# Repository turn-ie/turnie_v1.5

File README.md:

# turnie v1.5

Waveshare **ESP32-S3-Matrix**（8x8 LED）に自作のシールド基板を重ねた turnie。
すれ違った turnie どうしで、BLE5 拡張アドバタイズを使ってピクセルアートや文字を交換する。
基板、筐体（HP MJF PA12 ＋ アクリルの天板）、ファームウェアをまとめたリポジトリ。

## ディレクトリ構成

| ディレクトリ | 内容 |
|---|---|
| `hardware/` | KiCad プロジェクト（シールド基板 r2）、BOM、ガーバー（`production/`）、回路図 PDF（`out_20261115/`） |
| `enclosure/case_r2_20261120/` | 筐体 r2（STEP と、生成・干渉確認用の CadQuery スクリプト） |
| `enclosure/fdm_20261119/` | FDM 試作用の筐体（STEP、STL、スクリプト） |
| `firmware/` | ファームウェア（PlatformIO、ESP32-S3）。通信仕様は `firmware/COMMUNICATION_SPEC.md` |

## ハードウェア

| 部品 | 内容 |
|---|---|
| MCU / LED | Waveshare ESP32-S3-Matrix（8x8 WS2812B、IMU QMI8658） |
| 充電 | MCP73831（USB-C はモジュールの受け口を使う） |
| 電源 | SW2 スライドスイッチ ＋ SW1 で入る電源ラッチ（Q1 P-FET、IO2 で保持） |
| ボタン SW1 | 一般的な 6x6 mm タクトスイッチ（高さ 5 mm）＋ 3D プリントのキャップ |
| 電池 | LiPo 36 x 24.5 x 5.6 mm |
| 筐体 | 42.99 x 30.93 x 17.60 mm、HP MJF PA12、天板はアクリル 2.0 mm |

## 関連リポジトリ

- [turnie_device_v1.5](https://github.com/turn-ie/turnie_device_v1.5)：v1.5 のファームウェア（このリポジトリの `firmware/` は r2 基板向けの版）
- [turnie_app](https://github.com/turn-ie/turnie_app)：iOS アプリ
- [turnie_garber](https://github.com/turn-ie/turnie_garber)：初期のシールド基板のガーバー

## 備考

- 画像は KiCad の 3D ビュー（シールド基板 r2 ＋ ESP32-S3-Matrix）。

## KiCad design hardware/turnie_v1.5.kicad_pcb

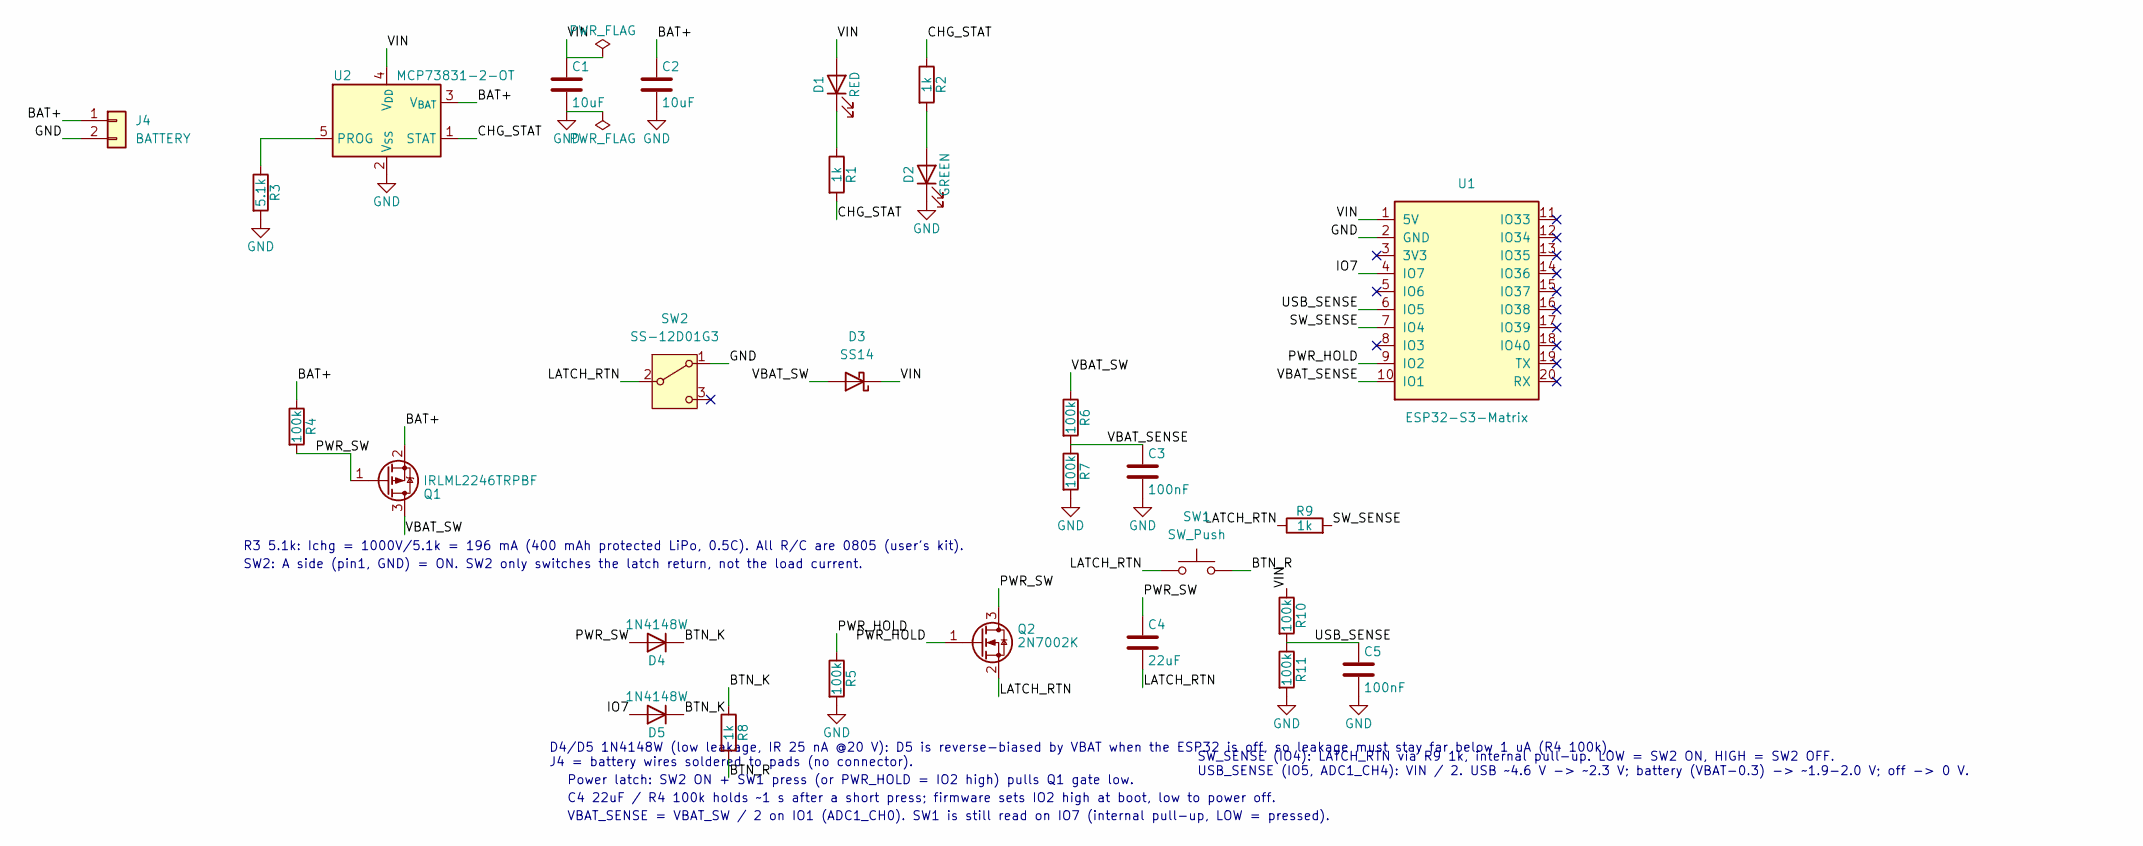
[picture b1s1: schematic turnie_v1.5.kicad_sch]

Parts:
C1, C2: 10uF; C_0805_2012Metric_Pad1.18x1.45mm_HandSolder; MPN 0805 10uF ≥10V X5R/X7R
C3, C5: 100nF; C_0805_2012Metric_Pad1.18x1.45mm_HandSolder; MPN 0805 100nF
C4: 22uF; C_0805_2012Metric_Pad1.18x1.45mm_HandSolder; MPN 0805 22uF ≥10V X5R/X7R
D1: RED; LED_0805_2012Metric_Pad1.15x1.40mm_HandSolder; MPN OSR50805C1C
D2: GREEN; LED_0805_2012Metric_Pad1.15x1.40mm_HandSolder; MPN OSG50805C1C
D3: SS14; D_SMA; MPN SS14
D4, D5: 1N4148W; D_SOD-123; MPN 1N4148W (PANJIT) SOD-123
J4: BATTERY; SolderPads_Battery_1x02_P2.54mm_Drill1.0mm; MPN solder pads, 1=BAT+ 2=GND
Q1: IRLML2246TRPBF; SOT-23; MPN IRLML2246TRPBF
Q2: 2N7002K; SOT-23; MPN 2N7002K
R1, R2, R8, R9: 1k; R_0805_2012Metric_Pad1.20x1.40mm_HandSolder; MPN 0805 1k
R3: 5.1k; R_0805_2012Metric_Pad1.20x1.40mm_HandSolder; MPN 0805 5.1k (1% 推奨)
R4, R5, R6, R7, R10, R11: 100k; R_0805_2012Metric_Pad1.20x1.40mm_HandSolder; MPN 0805 100k
SW1: SW_Push; SW_PUSH_6mm_H5mm; MPN generic 6x6x5mm THT tact
SW2: SS-12D01G3; SW_Slide_SPDT_JinBeiLi_SS-12D01G3_Akizuki_115704; MPN SS-12D01G3
U1: ESP32-S3-Matrix; Waveshare_ESP32-S3-Matrix; MPN Waveshare ESP32-S3-Matrix
U2: MCP73831-2-OT; SOT-23-5_HandSoldering; MPN MCP73831T-2ATI/OT

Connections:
/BAT+: C2.1, J4.1, Q1.2 (S), R4.1, U2.3 (V_{BAT})
/BTN_K: D4.1 (K), D5.1 (K), R8.1
/BTN_R: R8.2, SW1.2
/CHG_STAT: R1.2, R2.1, U2.1 (STAT)
/IO7: D5.2 (A), U1.4 (IO7)
/LATCH_RTN: C4.2, Q2.2 (S), R9.1, SW1.1, SW2.2 (B)
/PWR_HOLD: Q2.1 (G), R5.1, U1.9 (IO2)
/PWR_SW: C4.1, D4.2 (A), Q1.1 (G), Q2.3 (D), R4.2
/SW_SENSE: R9.2, U1.7 (IO4)
/USB_SENSE: C5.1, R10.2, R11.1, U1.6 (IO5)
/VBAT_SENSE: C3.1, R6.2, R7.1, U1.10 (IO1)
/VBAT_SW: D3.2 (A), Q1.3 (D), R6.1
/VIN: C1.1, D1.2 (A), D3.1 (K), R10.1, U1.1 (5V), U2.4 (V_{DD})
GND: C1.2, C2.2, C3.2, C5.2, D2.1 (K), J4.2, R3.2, R5.2, R7.2, R11.2, SW2.1 (A), U1.2 (GND), U2.2 (V_{SS})
unnamed: D1.1 (K), R1.1
unnamed: D2.2 (A), R2.2
unnamed: R3.1, U2.5 (PROG)

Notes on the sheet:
SW_SENSE (IO4): LATCH_RTN via R9 1k, internal pull-up. LOW = SW2 ON, HIGH = SW2 OFF. USB_SENSE (IO5, ADC1_CH4): VIN / 2. USB ~4.6 V -> ~2.3 V; battery (VBAT-0.3) -> ~1.9-2.0 V; off -> 0 V.
D4/D5 1N4148W (low leakage, IR 25 nA @20 V): D5 is reverse-biased by VBAT when the ESP32 is off, so leakage must stay far below 1 uA (R4 100k). J4 = battery wires soldered to pads (no connector).
SW2: A side (pin1, GND) = ON. SW2 only switches the latch return, not the load current.
R3 5.1k: Ichg = 1000V/5.1k = 196 mA (400 mAh protected LiPo, 0.5C). All R/C are 0805 (user's kit).
C4 22uF / R4 100k holds ~1 s after a short press; firmware sets IO2 high at boot, low to power off.
Power latch: SW2 ON + SW1 press (or PWR_HOLD = IO2 high) pulls Q1 gate low.
VBAT_SENSE = VBAT_SW / 2 on IO1 (ADC1_CH0). SW1 is still read on IO7 (internal pull-up, LOW = pressed).

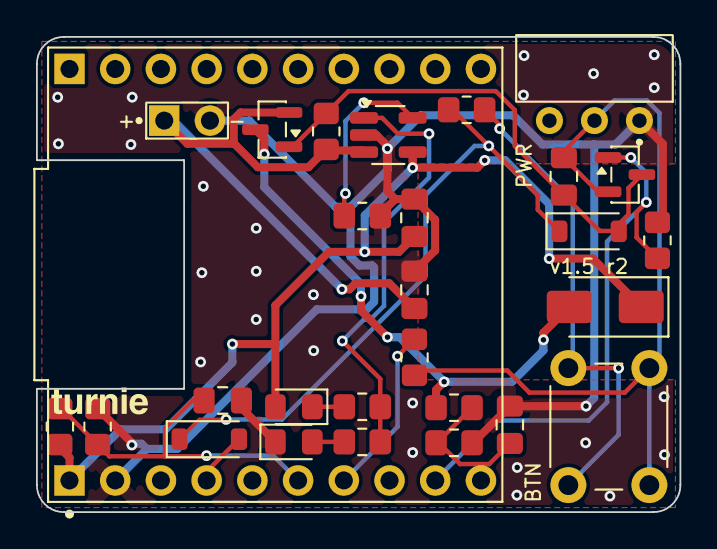
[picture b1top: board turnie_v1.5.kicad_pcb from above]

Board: 2 copper layers, 35.8 x 26.4 mm, 28 parts (0 on the bottom side), 17 nets.

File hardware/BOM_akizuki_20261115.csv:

Ref,値,秋月コード,品名（秋月の表記）,メーカー型番,パッケージ/フットプリント,1枚あたり個数,販売単位と価格(税込),備考
U2,MCP73831-2,113288,超小型単セル用リチウムイオン・リチウムポリマー充電コントローラー MCP73831-2ATI/OT,MCP73831T-2ATI/OT,SOT-23-5 (HandSoldering),1,¥120/1個,
Q1,IRLML2246TRPBF,106048,PchMOSFET IRLML2246TRPBF,IRLML2246TRPBF,SOT-23,1,¥250/10個,AO3401A は秋月に無いため置換。ピン 1=G 2=S 3=D、Vgs(th) -0.4〜-1.1V
Q2,2N7002K,104256,NchMOSFET 60V300mA 2N7002K,2N7002K (PANJIT),SOT-23,1,¥200/40個,
D1,赤LED,106419,赤色チップLED 2012 625nm 150mcd,OSR50805C1C,0805 (2012),1,¥150/10個,充電中に点灯
D2,緑LED,106423,緑色チップLED 2012 525nm 400mcd,OSG50805C1C,0805 (2012),1,¥200/10個,充電完了で点灯
D3,SS14,113240,表面実装用ショットキーバリアダイオード 40V1A SS14,SS14 (PANJIT),SMA,1,¥150/20個,
"D4,D5",1N4148W,116985,高速スイッチング・ダイオード 1N4148W,1N4148W (PANJIT),SOD-123,2,¥160/40個,逆電流 最大 25nA @20V (25℃)、150℃で最大 30µA @25V。BAT54CT の置き換え
"R1,R2,R8,R9",1kΩ,手持ちキット,0805 チップ抵抗,—,0805 (2012),4,—,秋月では購入しない
R3,5.1kΩ,手持ちキット,0805 チップ抵抗（1% 推奨）,—,0805 (2012),1,—,充電電流 約196mA
"R4,R5,R6,R7,R10,R11",100kΩ,手持ちキット,0805 チップ抵抗,—,0805 (2012),6,—,
"C1,C2",10µF,手持ちキット,0805 積層セラミック ≥10V X5R/X7R,—,0805 (2012),2,—,モジュール下に入るので厚さ 1.25mm 以下
"C3,C5",100nF,手持ちキット,0805 積層セラミック,—,0805 (2012),2,—,
C4,22µF,手持ちキット,0805 積層セラミック ≥10V X5R/X7R,—,0805 (2012),1,—,電源ラッチの保持用
SW1,タクトスイッチ,,一般的な 6×6 mm タクトスイッチ（背の低い型、高さ 5 mm）,generic 6x6x5mm THT tact,THT 6×6×5mm 4ピン（SW_PUSH_6mm_H5mm）,1,手持ち,2026-11-20 に 9.5 mm（TVDP01-095BB1、117166）から変更。足の配置 6.5×4.5mm は同じ。上に 3DP のキャップ（Fusion「turnie_ボタン修正版」のスイッチカバーv2_3.7）
SW2,スライドスイッチ,115704,スライドスイッチ 1回路2接点 基板用 横向き SS-12D01G3,SS-12D01G3,THT 3ピン 2.5mm,1,¥20/1個,定格 30V 0.3A（ラッチの戻り線だけを切るので負荷電流は流れない）
J4,電池の線,不要,（コネクタなし。電池の線を穴に直接はんだ付け）,—,THT パッド 2 個 2.54mm,—,—,1=BAT+（角パッド）、2=GND。モジュールを付ける前にはんだ付けする
(U1取付),2.54mmピンヘッダー,100167,ピンヘッダー 1×40 (40P),PH-1x40SG,10ピン×2に切って使用,1,¥35/1個,商品ページは未確認（一覧のみで確認）
U1,ESP32-S3-Matrix,秋月に無し,Waveshare ESP32-S3-Matrix,—,モジュール,1,—,スイッチサイエンス等で購入
BT,LiPo 400mAh 保護回路付き,秋月に無し,(v4 と同じ電池),—,—,1,—,秋月では保護回路付き LiPo を見つけられず

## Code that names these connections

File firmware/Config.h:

#pragma once
#include <Arduino.h>

// ============================================================
// Hardware Pins
// ============================================================
constexpr int PIN_MATRIX = 14;   // NeoMatrix データ
constexpr int PIN_BTN_BOOT = 0;  // BOOT ボタン（GPIO0）。v1.5r2 ではモジュールの裏で基板側を向くので、組み立て後は押せない

// v1.5r2 シールド基板（2026-11-15 作り直し、turnie_v1.5/作業記録_20261115_刷新.md 8 章・12.4 節）
constexpr int PIN_BTN_USER   = 7;  // SW1（INPUT_PULLUP、押すと約 0.55 V = LOW）。SW2 が OFF のときは読めない
constexpr int PIN_PWR_HOLD   = 2;  // 電源の保持（H で保持、L で切る）
constexpr int PIN_SW_SENSE   = 4;  // SW2 の状態（INPUT_PULLUP、L = ON、H = OFF）
constexpr int PIN_USB_SENSE  = 5;  // VIN / 2（ADC1_CH4）
constexpr int PIN_VBAT_SENSE = 1;  // 電池電圧（VBAT_SW）/ 2（ADC1_CH0）

// ============================================================
// Power (v1.5r2)
// ============================================================
constexpr float USB_DETECT_MARGIN_V = 0.15f;  // VIN > 電池電圧 + この値 なら USB あり
constexpr float LOW_BATT_OFF_V = 3.50f;       // 電池だけで動いているとき、これを下回ったら切る（3.5 V 前後でモジュールの LDO が持たなくなる）
constexpr int   LOW_BATT_CONFIRM_COUNT = 5;   // 1 秒ごとに読み、この回数続けて下回ったら確定
constexpr unsigned long POWER_OFF_HOLD_MS     = 3000;   // 電池のとき：ボタンをこの時間押し続けると電源を切る
constexpr unsigned long OTA_HOLD_MS           = 5000;   // USB のとき：この時間押してから離すと OTA モード（BOOT 短押しの代わり）
constexpr unsigned long FACTORY_RESET_HOLD_MS = 10000;  // USB のとき：この時間押し続けると初期化（BOOT 長押しの代わり）
// 操作も受信もない状態がこの時間続いたら、電池のときは自分で電源を切る。0 = 使わない。
// すれ違いの受信は電源が入っている間しかできないので、既定では使わない。
constexpr unsigned long AUTO_OFF_MS = 0;

// ============================================================
// Display (8x8 LED Matrix)
// ============================================================
constexpr int MATRIX_WIDTH = 8;
constexpr int MATRIX_HEIGHT = 8;
constexpr int MATRIX_PIXEL_COUNT = MATRIX_WIDTH * MATRIX_HEIGHT;
constexpr int MATRIX_RGB_BYTES = MATRIX_PIXEL_COUNT * 3;

// 明るさは全モード共通で MOTION_BRIGHTNESS（スマホ設定値）を使う。
constexpr uint16_t TEXT_SCROLL_DELAY_MS = 70;

// ============================================================
// Timing
// ============================================================
constexpr unsigned long LOOP_TICK_MS = 16;          // ~60 fps
constexpr unsigned long RX_DISPLAY_HOLD_MS = 4500;  // 受信表示の保持時間
constexpr unsigned long RX_IGNORE_MS = 5000;        // 一度受信したら、この時間は内容に関わらず後続の受信を全て無視する
constexpr unsigned long RX_SAME_REJECT_MS = 180000; // 直前に受け付けたのと同じ内容がこの時間（5分）以内に届いた場合、完全にリジェクトする（表示も保存も返信もしない）。時間を超えれば同じ内容でも改めて受け付ける。

// 受信履歴の閲覧モード（USER ボタン操作）
constexpr unsigned long BROWSE_LONG_PRESS_MS = 800;    // 長押し判定（閲覧モード開始/終了）
constexpr unsigned long BUTTON_DEBOUNCE_MS = 50;       // 短押しのチャタリング除去
constexpr unsigned long BROWSE_TIMEOUT_MS = 30000;     // 無操作でこの時間経過したら通常へ戻る
constexpr unsigned long BOOT_RESET_LONG_PRESS_MS = 1500; // BOOT長押しでJSONデータをリセット

// ============================================================
// Storage (内部フラッシュ - LittleFS)
// ============================================================
constexpr const char *SD_OWN_JSON = "/data.json";

// ============================================================
// BLE Identity
// ============================================================
constexpr const char *BLE_DEVICE_NAME = "turnie"; // デバイスごとに変更
constexpr uint16_t BLE_COMPANY_ID = 0xFFFF;       // turnie 間の識別子

// ============================================================
// BLE5 Extended Advertising
// ============================================================
constexpr uint8_t BLE_EXT_ADV_HANDLE =
    0; // デバイス間ブロードキャスト（non-connectable）
constexpr uint8_t BLE_GATT_ADV_HANDLE =
    1; // スマホ向け GATT 広告（connectable）
constexpr uint32_t BLE_EXT_ADV_INTERVAL = 0x00C0; // 120 ms (n * 0.625 ms)
constexpr int8_t BLE_EXT_ADV_TX_POWER = 8;        // dBm

// BLE5 Extended Scan
constexpr uint16_t BLE_EXT_SCAN_INTERVAL = 0x0050; // 50 ms
constexpr uint16_t BLE_EXT_SCAN_WINDOW = 0x0030;   // 30 ms

// ============================================================
// BLE GATT (smartphone interface)
// ============================================================
constexpr uint16_t GATT_APP_ID = 0;
constexpr const char *GATT_SVC_UUID = "12345678-1234-1234-1234-1234567890ab";
constexpr const char *GATT_RX_UUID = "abcd1234-5678-90ab-cdef-1234567890ab";
constexpr const char *GATT_TX_UUID = "abcd1234-5678-90ab-cdef-1234567890ac";

// ============================================================
// Inbox (received messages, RAM ring buffer)
// ============================================================
constexpr size_t INBOX_CAPACITY = 30;

// ============================================================
// BLE Settings
// ============================================================
// RSSI の閾値（これより弱い信号は無視する）
// 密着状態で -30 ~ -40, 1m離れて -60 程度
// -128 = 実質すべての受信を許可（int8_t の最小値）
constexpr int8_t BLE_RSSI_MIN = -128;

// ============================================================
// Animation Hue & Settings (per-device config)
// ============================================================
// 色相 H は 0–360（度）。スマホ(setting.json)から送られてくる値もこの範囲。
//   turnie1=127(赤ピンク) / turnie2=298(青) / turnie3=6(緑) / turnie4=104(黄)
constexpr uint8_t DEFAULT_BRIGHTNESS_PERCENT = 25;
constexpr uint8_t DEFAULT_MOTION_BRIGHTNESS = (DEFAULT_BRIGHTNESS_PERCENT * 255) / 100;

extern uint16_t MOTION_HUE;
extern uint8_t MOTION_BRIGHTNESS;
extern uint8_t MOTION_ANIM;

constexpr int DEVICE_NAME_MAX = 32;
extern char DEVICE_NAME[DEVICE_NAME_MAX];

// 出身地（スマホ setting.json の hometown）。任意の文字列。
constexpr int HOMETOWN_MAX = 64;
extern char HOMETOWN[HOMETOWN_MAX];

constexpr const char *SD_SETTING_JSON = "/setting.json";
constexpr const char *SD_INBOX_JSON = "/inbox.json";

// OTA / WiFi の認証情報は Secrets.h に分離（Git には含めない）。
//   初回は Secrets.h.example をコピーして作成する: cp Secrets.h.example Secrets.h
//   定義: OTA_WIFI_SSID/PASS(1..3), OTA_HOSTNAME, OTA_PASSWORD
#include "Secrets.h"

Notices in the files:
hardware/turnie_v1.5.kicad_pcb:
turnie © All rights reserved.
